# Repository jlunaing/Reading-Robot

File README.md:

### Reading-Robot
A socially assistive robot that can help students with reading practice. For 
instructions on how to use the system, see [user guide](user_guide.md).

## Background

There is an insufficient availability of human experts to assist students in 
reading competency and comprehension. The goal of this porject is to create an 
socially assistive robot that can be used by therapists, teachers, and parents 
to help children and adults develop and practice reading comprehension skills 
while they do not have access to specialists. This robot enables the user to 
improve their reading skills without an educator present and allows educators to 
review the student's performance remotely. 

The design includes a robot and a phone running an app. The basic tasks that the
robot performs is to give instructions for the reading sessions and prompts the
student to start reading. The robot then records the passage read to allow a 
teacher or therapist to review it at a later time. Then, the robot asks 
questions based on the reading and gives constructive feedback based on the 
correctness of the responses. During the interaction, the robot has the ability
to tilt the phone back and forth, wiggle its antennas, and show different faces
on its LED screen. This gives the interaction with the user more embodiment.

## Making a Reading Robot

### Part List
To make one of this robots, the following parts are needed:

#### General parts:
- 3D printed parts (see [CAD files](src/hardware/cad/solidworks/))
- Android phone (1)
- Bluetooth headset (optional) (1)
- Pimoroni Unicorn Hat HD LED array (1)					

#### Actuation:
- TowerPro MG995 Digital servo motor (1)				
- Uxcell 6V DC motor, 100-rpm (1)	
- Adafruit TB6612 motor driver board (1)					
- 6455K13 plastic ball bearing (2)					
- RB-Tib-11 Lynxmotion servo timing belt pulley (2)					
- 1254N22 MXL timing belt pulley (1)	

#### Fasteners:
- Tapered heat-set inserts:
  - 2-56 thread size (93365A110)			
  - 4-40 thread size (93365A120)
- Screws:
  - 18-8 screw 1/2'' long (91772A110)
  - 2-56 screw 11/32'' long (91772A506)
  - 2-56 screw 3/16'' long (91772A076)
  - 4-40 screw 3/4'' long (91772A113)			
- Neodymium magnet 1/4'' (5862K103) (8)
- 18-8 binding barrel & screw (99637A307) (1)
- Nylon spacers (90176A114)
- 5/8'' Long Dowel Pin (98381A539)					
- 2 – 1/8'' Long Dowel Pin (98381A325)					

#### Electronics:
- Raspberry Pi 4 + SD card
- Custom PCB for power distribution (see [board files](src/hardware/pcb/))
- 40-pin connector (S9200-ND) (2)
- USB-C breakout board (1568-1958-ND)
- JST RCY connector, 2-pin (PRT-10501)					
- JST jumper 2-wire (PRT-09914)					
- JST jumper 3-wire (PRT-09915)

### Power:
- AUKEY USB-C 2 port charger					
- AC adapter/power supply (2)					
- USB 3.1 type C M-F data extension cable (2)					

The assembly of the robot can be facilitated by refering to the assembly drawings
or the [CAD files](src/hardware/cad/solidworks/). Some reference images are 
included below.

### Code

See [source files](src/firmware/python/) for details.

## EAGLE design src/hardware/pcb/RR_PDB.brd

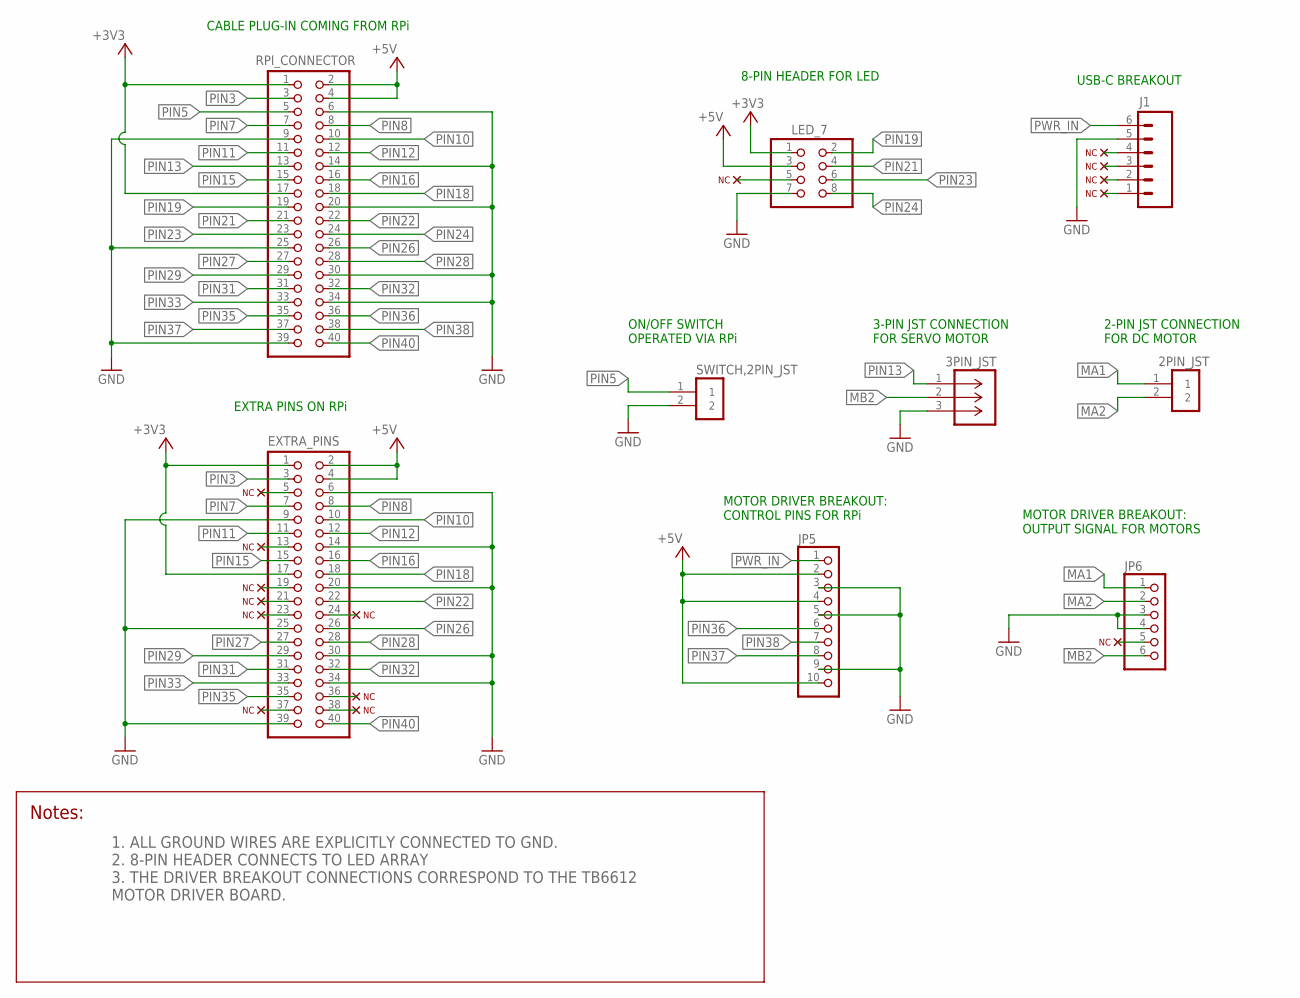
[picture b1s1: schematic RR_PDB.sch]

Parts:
2PIN_JST: B2B-PH-K-S(LF)(SN); JST_B2B-PH-K-S(LF)(SN)
3PIN_JST: B3B-PH-K-S(LF)(SN); CONN_B3B-PH-K-S(LF)(SN)_JST
EXTRA_PINS: PINHD-2X20; 2X20
J1: CONN_06NO_SILK_NO_POP; 1X06_NO_SILK
JP5: HEADER-1X10THICKER; 1X10_ROUND_76
JP6: PINHD-1X6CB; 1X06-CLEANBIG
LED_7: PINHD-2X4; 2X04
RPI_CONNECTOR: PINHD-2X20; 2X20
SWITCH,2PIN_JST: B2B-PH-K-S(LF)(SN); JST_B2B-PH-K-S(LF)(SN)

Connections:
+3V3: EXTRA_PINS.1, EXTRA_PINS.17, LED_7.1, RPI_CONNECTOR.1, RPI_CONNECTOR.17
+5V: EXTRA_PINS.2, EXTRA_PINS.4, JP5.2, JP5.4, JP5.10, LED_7.3, RPI_CONNECTOR.2, RPI_CONNECTOR.4
CC1: J1.4
CC2: J1.1
D+: J1.2
D-: J1.3
GND: 3PIN_JST.3, EXTRA_PINS.6, EXTRA_PINS.9, EXTRA_PINS.14, EXTRA_PINS.20, EXTRA_PINS.25, EXTRA_PINS.30, EXTRA_PINS.34, EXTRA_PINS.39, J1.5, JP5.3, JP5.5, JP5.9, JP6.3, JP6.4, LED_7.7, RPI_CONNECTOR.6, RPI_CONNECTOR.9, RPI_CONNECTOR.14, RPI_CONNECTOR.20, RPI_CONNECTOR.25, RPI_CONNECTOR.30, RPI_CONNECTOR.34, RPI_CONNECTOR.39, SWITCH,2PIN_JST.2
MA1: 2PIN_JST.1, JP6.1
MA2: 2PIN_JST.2, JP6.2
MB2: 3PIN_JST.2, JP6.6
PIN3: EXTRA_PINS.3, RPI_CONNECTOR.3
PIN5: RPI_CONNECTOR.5, SWITCH,2PIN_JST.1
PIN7: EXTRA_PINS.7, RPI_CONNECTOR.7
PIN8: EXTRA_PINS.8, RPI_CONNECTOR.8
PIN10: EXTRA_PINS.10, RPI_CONNECTOR.10
PIN11: EXTRA_PINS.11, RPI_CONNECTOR.11
PIN12: EXTRA_PINS.12, RPI_CONNECTOR.12
PIN13: 3PIN_JST.1, RPI_CONNECTOR.13
PIN15: EXTRA_PINS.15, RPI_CONNECTOR.15
PIN16: EXTRA_PINS.16, RPI_CONNECTOR.16
PIN18: EXTRA_PINS.18, RPI_CONNECTOR.18
PIN19: LED_7.2, RPI_CONNECTOR.19
PIN21: LED_7.4, RPI_CONNECTOR.21
PIN22: EXTRA_PINS.22, RPI_CONNECTOR.22
PIN23: LED_7.6, RPI_CONNECTOR.23
PIN24: LED_7.8, RPI_CONNECTOR.24
PIN26: EXTRA_PINS.26, RPI_CONNECTOR.26
PIN27: EXTRA_PINS.27, RPI_CONNECTOR.27
PIN28: EXTRA_PINS.28, RPI_CONNECTOR.28
PIN29: EXTRA_PINS.29, RPI_CONNECTOR.29
PIN31: EXTRA_PINS.31, RPI_CONNECTOR.31
PIN32: EXTRA_PINS.32, RPI_CONNECTOR.32
PIN33: EXTRA_PINS.33, RPI_CONNECTOR.33
PIN35: EXTRA_PINS.35, RPI_CONNECTOR.35
PIN36: JP5.6, RPI_CONNECTOR.36
PIN37: JP5.8, RPI_CONNECTOR.37
PIN38: JP5.7, RPI_CONNECTOR.38
PIN40: EXTRA_PINS.40, RPI_CONNECTOR.40
PWR_IN: J1.6, JP5.1

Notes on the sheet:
MOTOR DRIVER BREAKOUT: OUTPUT SIGNAL FOR MOTORS
MOTOR DRIVER BREAKOUT: CONTROL PINS FOR RPi
2-PIN JST CONNECTION FOR DC MOTOR
3-PIN JST CONNECTION FOR SERVO MOTOR
CABLE PLUG-IN COMING FROM RPi
ON/OFF SWITCH OPERATED VIA RPi
EXTRA PINS ON RPi
8-PIN HEADER FOR LED
USB-C BREAKOUT
1. ALL GROUND WIRES ARE EXPLICITLY CONNECTED TO GND. 2. 8-PIN HEADER CONNECTS TO LED ARRAY 3. THE DRIVER BREAKOUT CONNECTIONS CORRESPOND TO THE TB6612 MOTOR DRIVER BOARD.

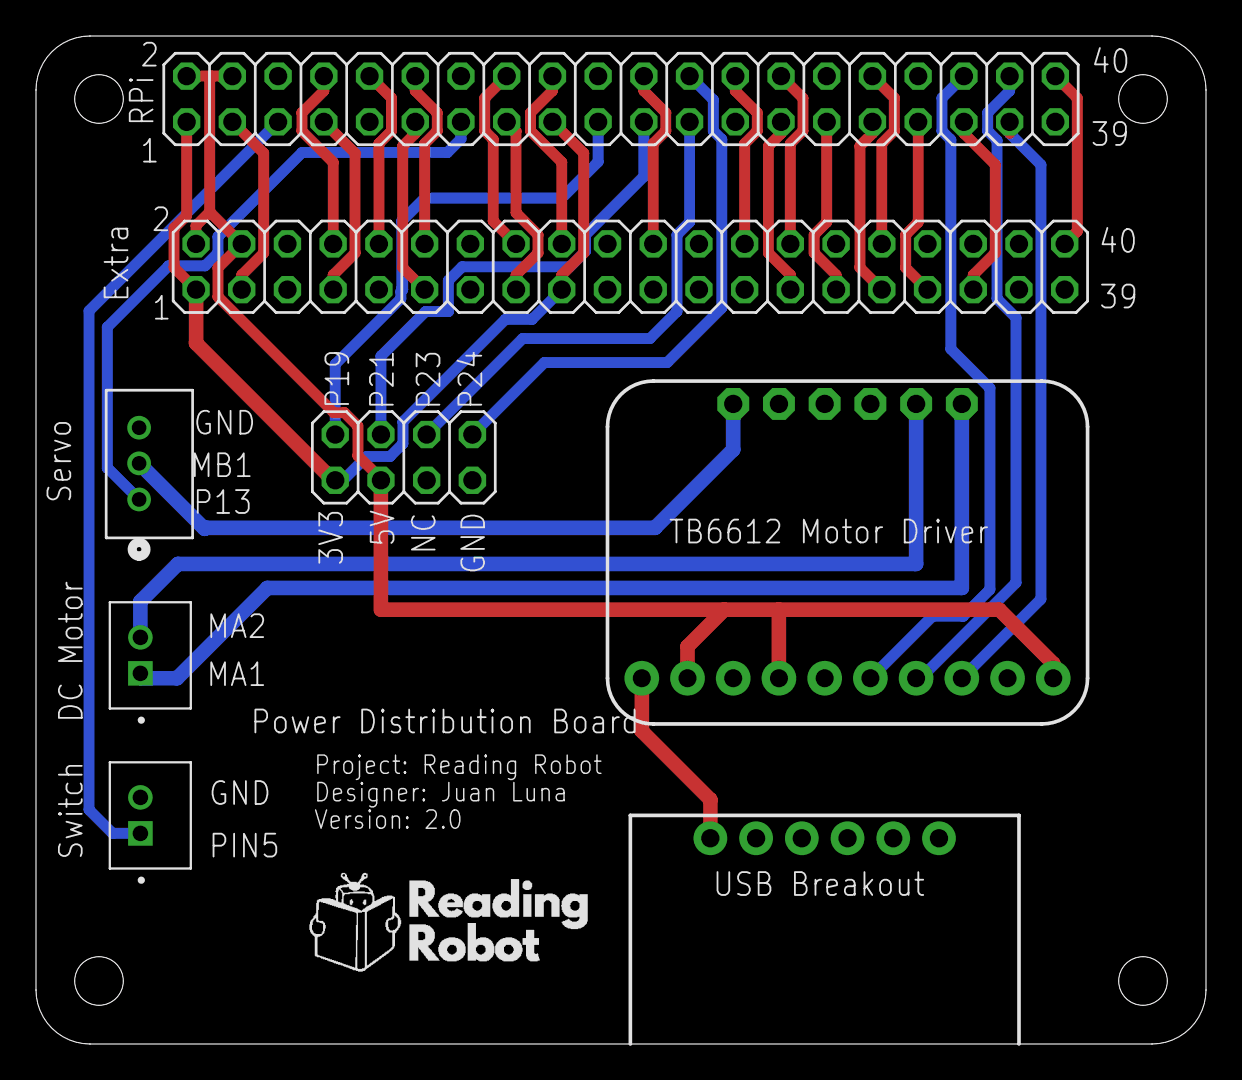
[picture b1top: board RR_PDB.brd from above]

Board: 2 copper layers, 65.0 x 56.0 mm, 9 parts (0 on the bottom side), 35 nets.

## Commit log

2023-05-10 Source files and documentation for Reading Robot project
2023-05-10 Updated documentation

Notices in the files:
parts and their libraries:
SparkFun-Connectors: Licensing: Creative Commons ShareAlike 4.0 International - https://creativecommons.org/licenses/by-sa/4.0
COPYRIGHT: Copyright (C) 2023 Ultra Librarian. All rights reserved.
